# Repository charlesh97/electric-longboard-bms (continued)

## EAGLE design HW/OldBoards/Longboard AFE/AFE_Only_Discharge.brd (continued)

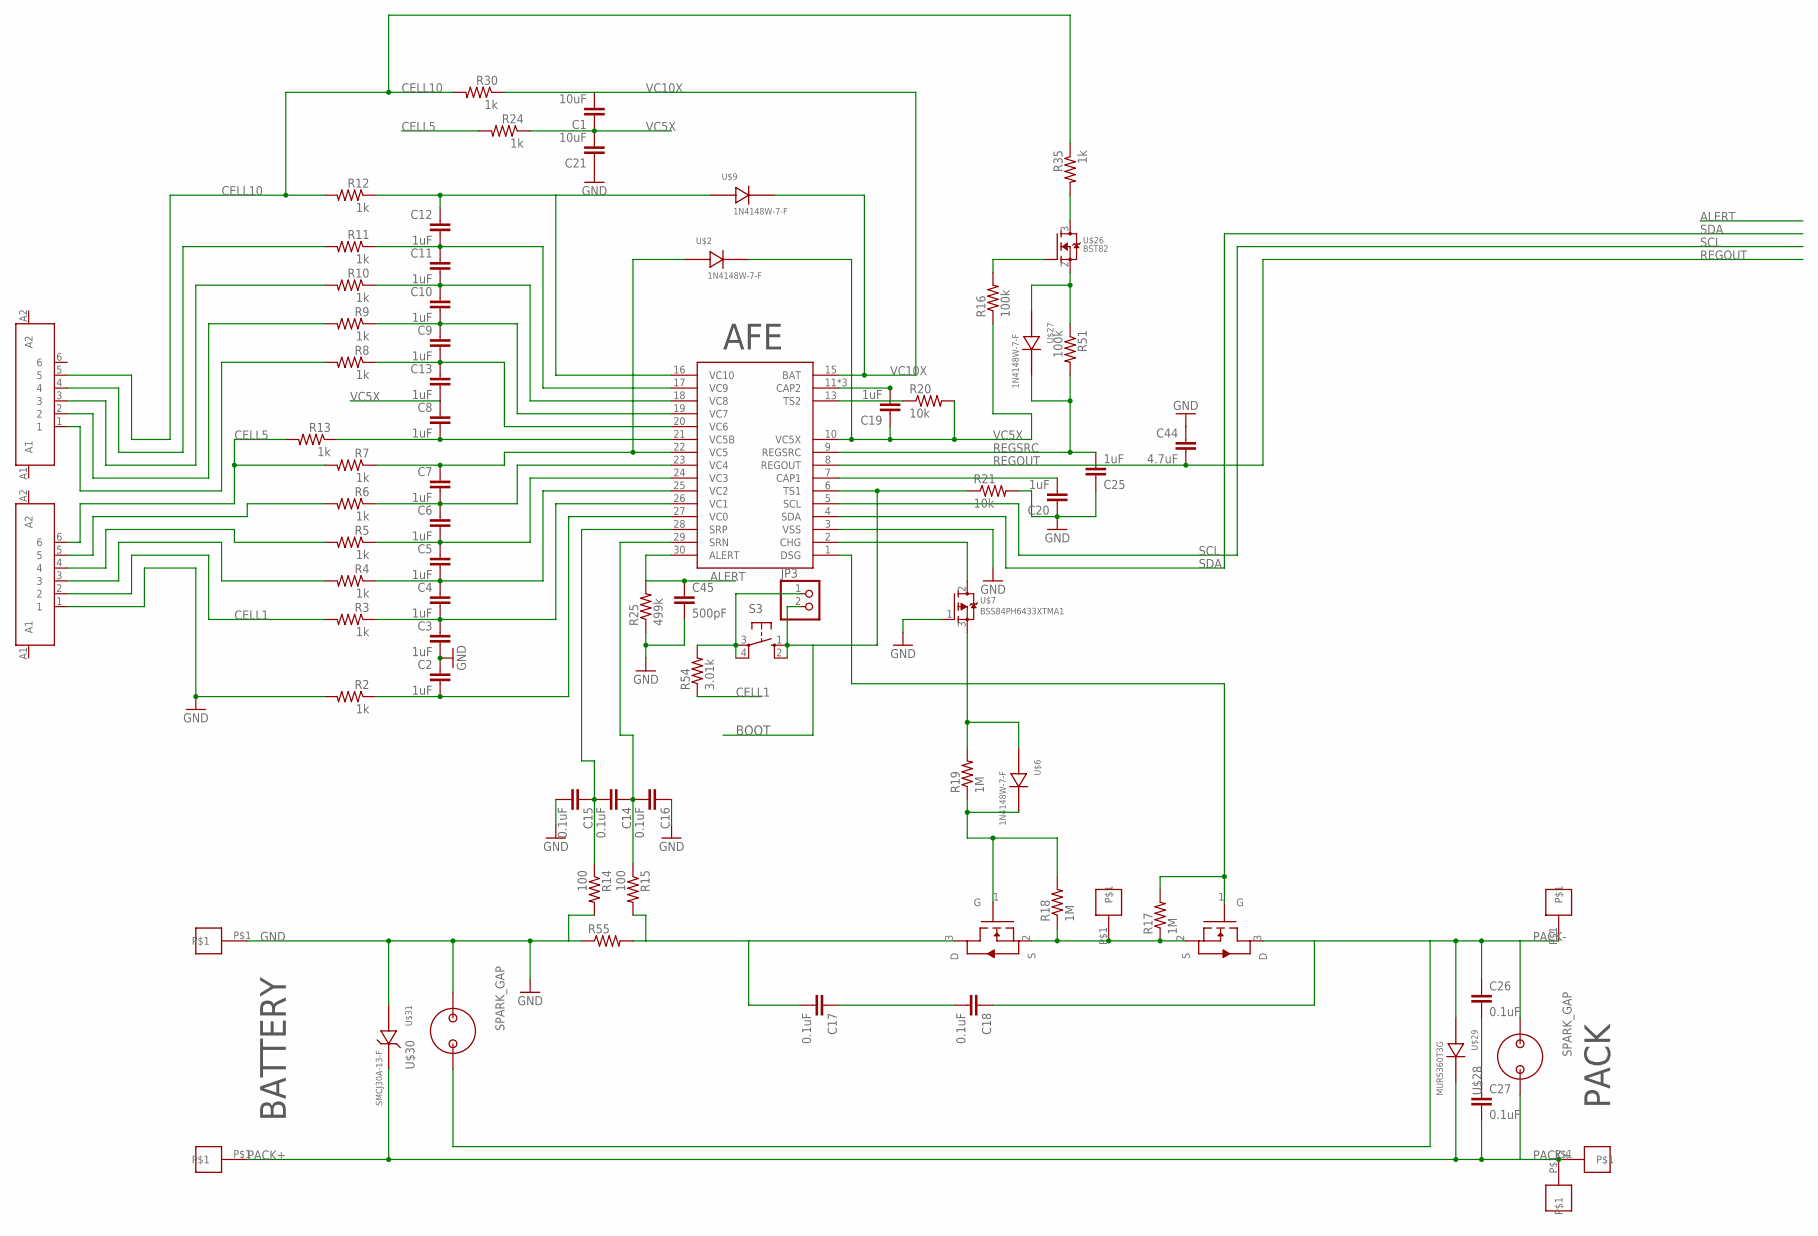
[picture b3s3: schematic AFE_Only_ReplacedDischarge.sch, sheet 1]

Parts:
C1, C21: 10uF; C1210
C2, C3, C4, C5, C6, C7, C8, C9, C10, C11, C12, C13, C19, C20, C25: 1uF; C0805
C14, C15, C16, C17, C18, C26, C27: 0.1uF; C0805
C44: 4.7uF; C0805
C45: 500pF; C0603
JP3: PINHD-1X2; 1X02
R2, R3, R4, R5, R6, R7, R8, R9, R10, R11, R12, R13, R24, R30, R35: 1k; R1206
R14, R15: 100; R0805
R16, R51: 100k; R0805
R17, R18, R19: 1M; R1206
R20, R21: 10k; R0805
R25: 499k; R0603
R54: 3.01k; R1206
R55: R-US_R2512; R2512
S3: 10-XX; B3F-10XX
U$1: BQ76930; SOIC-30
U$2, U$6, U$9, U$27: 1N4148W-7-F; SOD-123
U$3, U$35, U$36, U$37, U$38, U$39: PAD
U$4, U$5: AOB290L; TO-263
U$7: BSS84PH6433XTMA1; SOT23-3
U$24, U$33: JST_6PIN
U$26: BST82; SOT23-3
U$28, U$30: SPARK_GAP
U$29: MURS360T3G; SMC(DO-214AB)
U$31: SMCJ30A-13-F; SMB(DO-214AA)

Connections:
ALERT: C45.1, R25.2, U$1.30 (ALERT); also elsewhere on the board
BOOT: JP3.2, R21.1, S3.1 (S), S3.2 (S1), U$1.6 (TS1)
CELL1: R3.2, R54.1, U$33.2
CELL5: R7.2, R13.2, R24.2, U$33.6
CELL10: R12.2, R30.2, R35.1, U$24.5
GND: C2.1, C3.2, C15.2, C16.1, C20.1, C21.1, C25.1, C44.1, C45.2, R2.2, R14.2, R21.2, R25.1, R55.1, U$1.3 (VSS), U$3.P$1, U$7.1 (G), U$30.P$2, U$31.P$1 (1), U$33.1; also elsewhere on the board
unnamed: C3.1, C4.2, R3.1, U$1.26 (VC1)
unnamed: C4.1, C5.2, R4.1, U$1.25 (VC2)
unnamed: C5.1, C6.2, R5.1, U$1.24 (VC3)
unnamed: C6.1, C7.2, R6.1, U$1.23 (VC4)
unnamed: C7.1, R7.1, U$1.22 (VC5), U$2.P$1
unnamed: C8.2, R13.1, U$1.21 (VC5B)
unnamed: C9.1, C10.2, R9.1, U$1.19 (VC7)
unnamed: C10.1, C11.2, R10.1, U$1.18 (VC8)
unnamed: C11.1, C12.2, R11.1, U$1.17 (VC9)
unnamed: C12.1, R12.1, U$1.16 (VC10), U$9.P$1
unnamed: R5.2, U$33.4
unnamed: C2.2, R2.1, U$1.27 (VC0)
unnamed: C26.2, C27.1
unnamed: R4.2, U$33.3
unnamed: R6.2, U$33.5
unnamed: R8.2, U$24.1
unnamed: R9.2, U$24.2
unnamed: R10.2, U$24.3
unnamed: R11.2, U$24.4
unnamed: C9.2, C13.1, R8.1, U$1.20 (VC6)
unnamed: R16.2, U$26.1 (G)
unnamed: C20.2, U$1.7 (CAP1)
unnamed: C14.1, C16.2, R15.1, U$1.29 (SRN)
unnamed: JP3.1, R54.2, S3.3, S3.4 (P1)
unnamed: C14.2, C15.1, R14.1, U$1.28 (SRP)
unnamed: R18.2, R19.1, U$5.1 (G), U$6.P$2
unnamed: R19.2, U$6.P$1, U$7.3 (D)
unnamed: U$1.2 (CHG), U$7.2 (S)
unnamed: C17.1, C18.2
unnamed: C19.2, U$1.11 (CAP2), U$1.12 (CAP2), U$1.14 (CAP2)
unnamed: R20.1, U$1.13 (TS2)
unnamed: R51.1, U$26.2 (S), U$27.P$1
unnamed: R35.2, U$26.3 (D)
PACK+: C27.2, U$28.P$1, U$29.2, U$31.P$2 (2), U$35.P$1, U$36.P$1, U$39.P$1
REGOUT: C44.2, U$1.8 (REGOUT); also elsewhere on the board
REGSRC: C25.2, R51.2, U$1.9 (REGSRC), U$27.P$2
SCL: U$1.5 (SCL); also elsewhere on the board
SDA: U$1.4 (SDA); also elsewhere on the board
VC5X: C1.1, C8.1, C13.2, C19.1, C21.2, R16.1, R20.2, R24.1, U$1.10 (VC5X), U$2.P$2
VC10X: C1.2, R30.1, U$1.15 (BAT), U$9.P$2

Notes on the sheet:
BATTERY
PACK
AFE

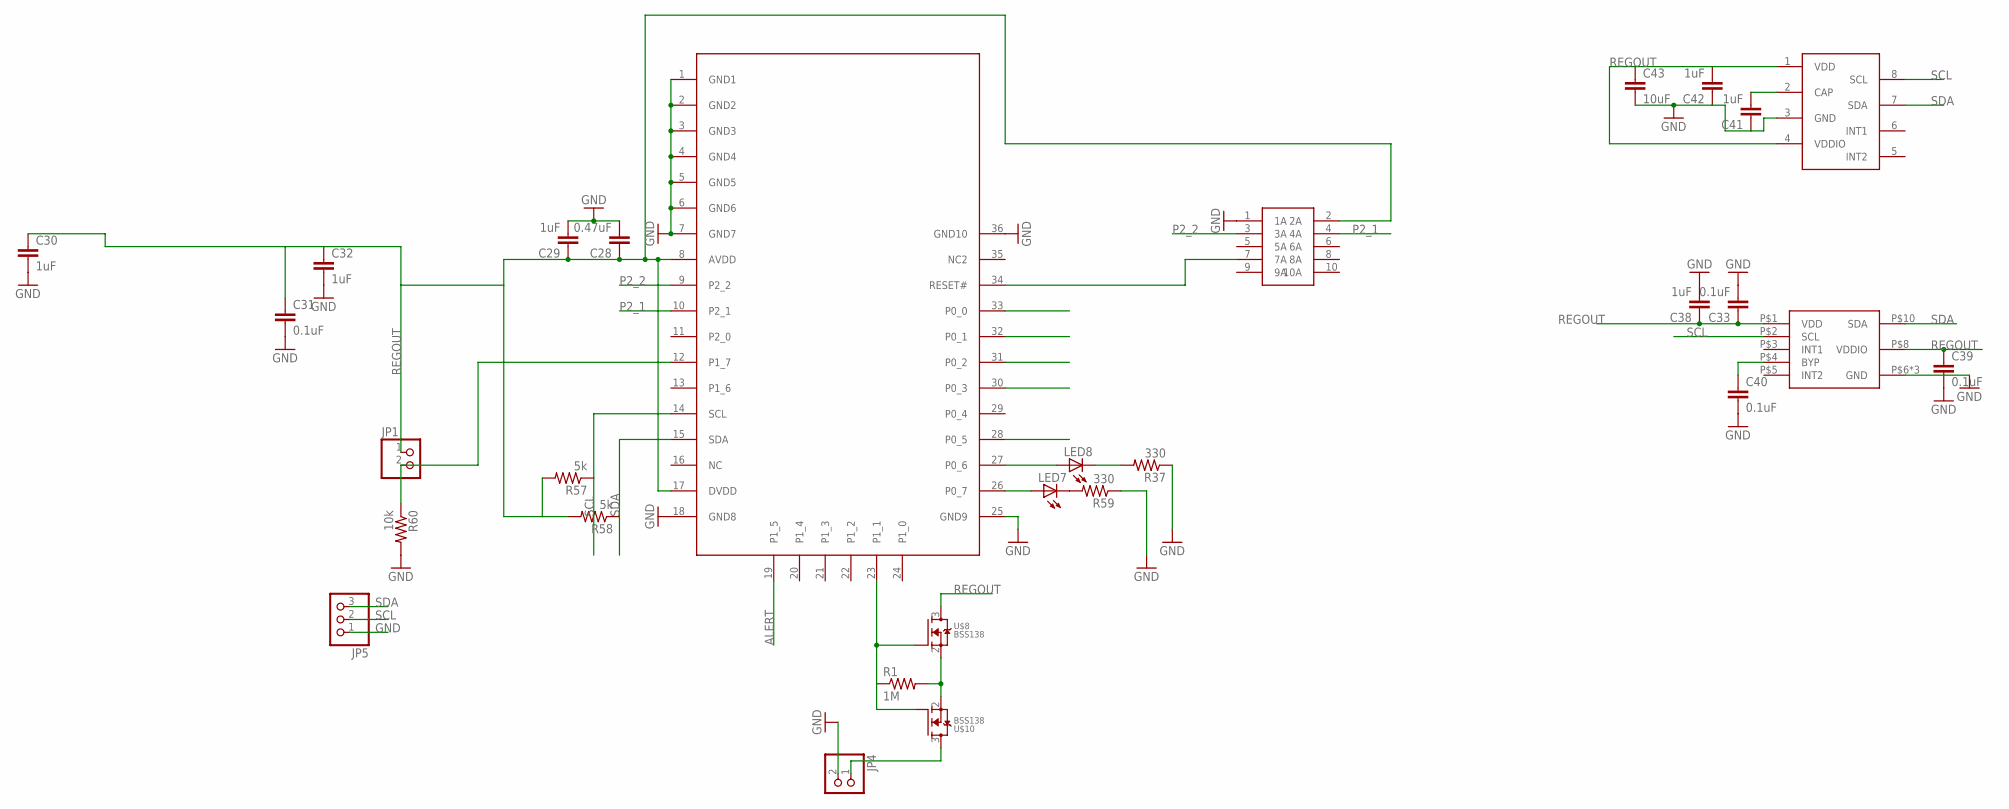
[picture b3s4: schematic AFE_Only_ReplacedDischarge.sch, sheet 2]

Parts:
C28: 0.47uF; C0402
C29, C30, C32, C38, C41, C42: 1uF; C0402
C31, C33, C39, C40: 0.1uF; C0402
C43: 10uF; C0603
JP1, JP4: PINHD-1X2; 1X02
JP5: PINHD-1X3; 1X03
LED7, LED8: LEDCHIP-LED0603; CHIP-LED0603
R1: 1M; R0402
R37, R59: 330; R0402
R57, R58: 5k; R0402
R60: 10k; R0402
U$8, U$10: BSS138; SOT23-3
U$20: BLE113; BLUEGIGA
U$22: RIBBON_10POS_MALE
U$25: MLP3115A2
U$32: MMA8653FC; 10-DFN2X2

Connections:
ALERT: U$20.19 (P1_5); also elsewhere on the board
CARD2: U$20.32 (P0_1)
CD: U$20.33 (P0_0)
CLK: U$20.28 (P0_5)
GND: C28.2, C29.2, C30.2, C31.2, C32.2, C33.2, C38.2, C39.2, C40.2, C41.1, C42.1, C43.2, JP4.2, JP5.1, R37.1, R59.1, R60.2, U$20.1 (GND1), U$20.2 (GND2), U$20.3 (GND3), U$20.4 (GND4), U$20.5 (GND5), U$20.6 (GND6), U$20.7 (GND7), U$20.18 (GND8), U$20.25 (GND9), U$20.36 (GND10), U$22.1 (1A), U$25.3 (GND), U$32.P$6 (GND), U$32.P$7 (GND), U$32.P$9 (GND); also elsewhere on the board
MISO: U$20.31 (P0_2)
MOSI: U$20.30 (P0_3)
unnamed: LED8.A, U$20.27 (P0_6)
unnamed: LED8.C, R37.2
unnamed: LED7.A, U$20.26 (P0_7)
unnamed: JP1.2, R60.1, U$20.12 (P1_7)
unnamed: LED7.C, R59.2
unnamed: U$20.34 (RESET#), U$22.7 (7A)
unnamed: C41.2, U$25.2 (CAP)
unnamed: C40.1, U$32.P$4 (BYP)
P2_1: U$20.10 (P2_1), U$22.4 (4A)
P2_2: U$20.9 (P2_2), U$22.3 (3A)
REGOUT: C28.1, C29.1, C30.1, C31.1, C32.1, C33.1, C38.1, C39.1, C42.2, C43.1, JP1.1, R57.2, R58.2, U$8.3 (D), U$20.8 (AVDD), U$20.17 (DVDD), U$22.2 (2A), U$25.1 (VDD), U$25.4 (VDDIO), U$32.P$1 (VDD), U$32.P$8 (VDDIO); also elsewhere on the board
SCL: JP5.2, R57.1, U$20.14 (SCL), U$25.8 (SCL), U$32.P$2 (SCL); also elsewhere on the board
SDA: JP5.3, R58.1, U$20.15 (SDA), U$25.7 (SDA), U$32.P$10 (SDA); also elsewhere on the board

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
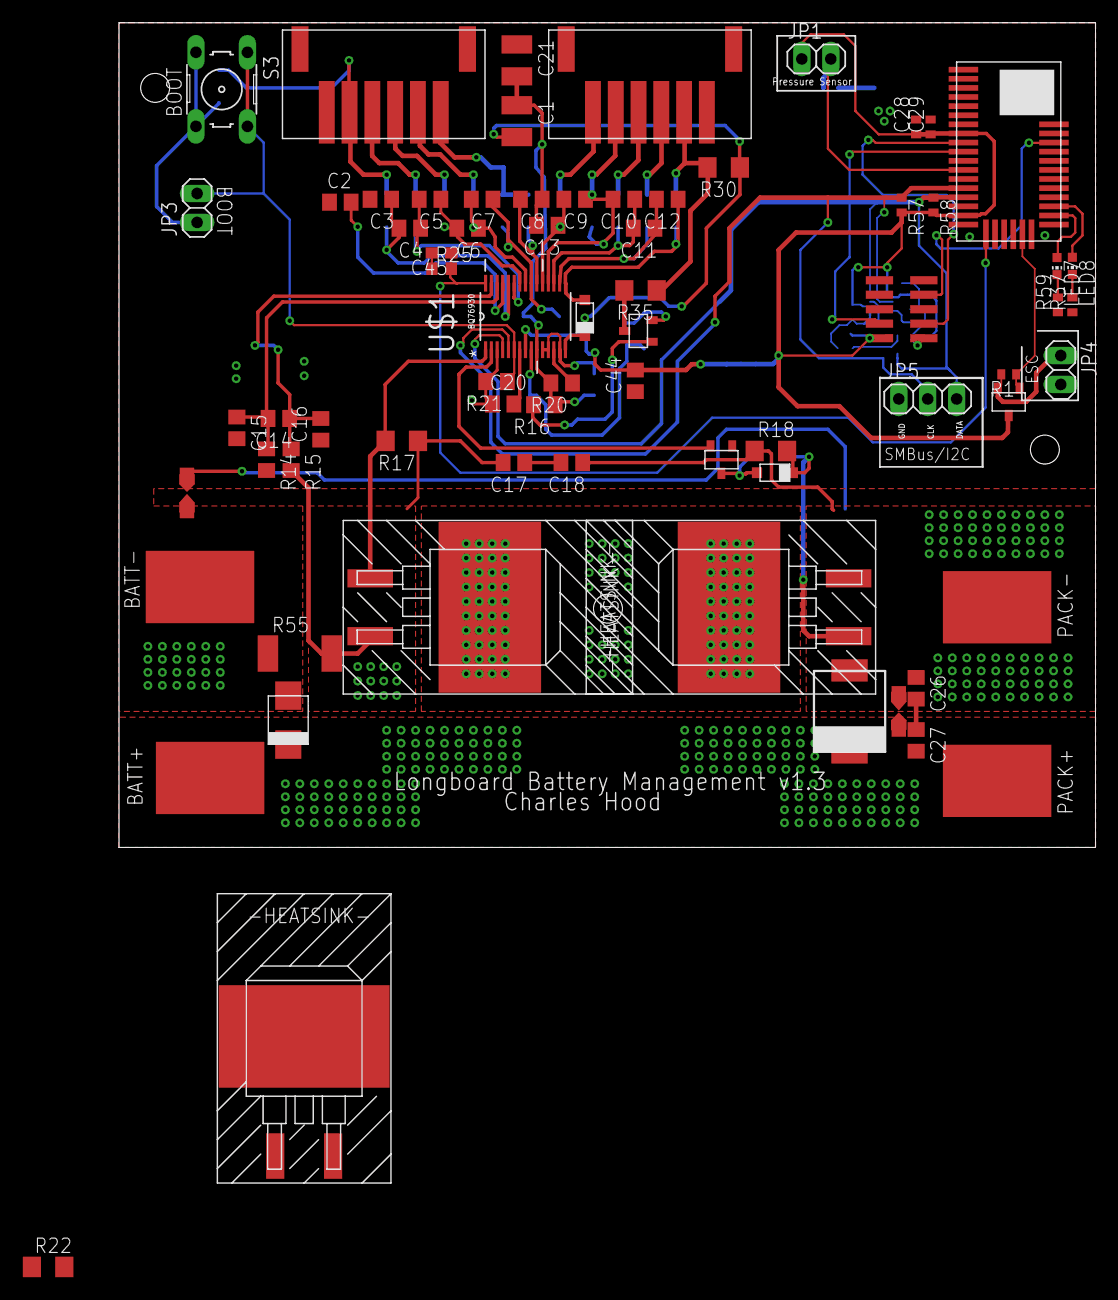
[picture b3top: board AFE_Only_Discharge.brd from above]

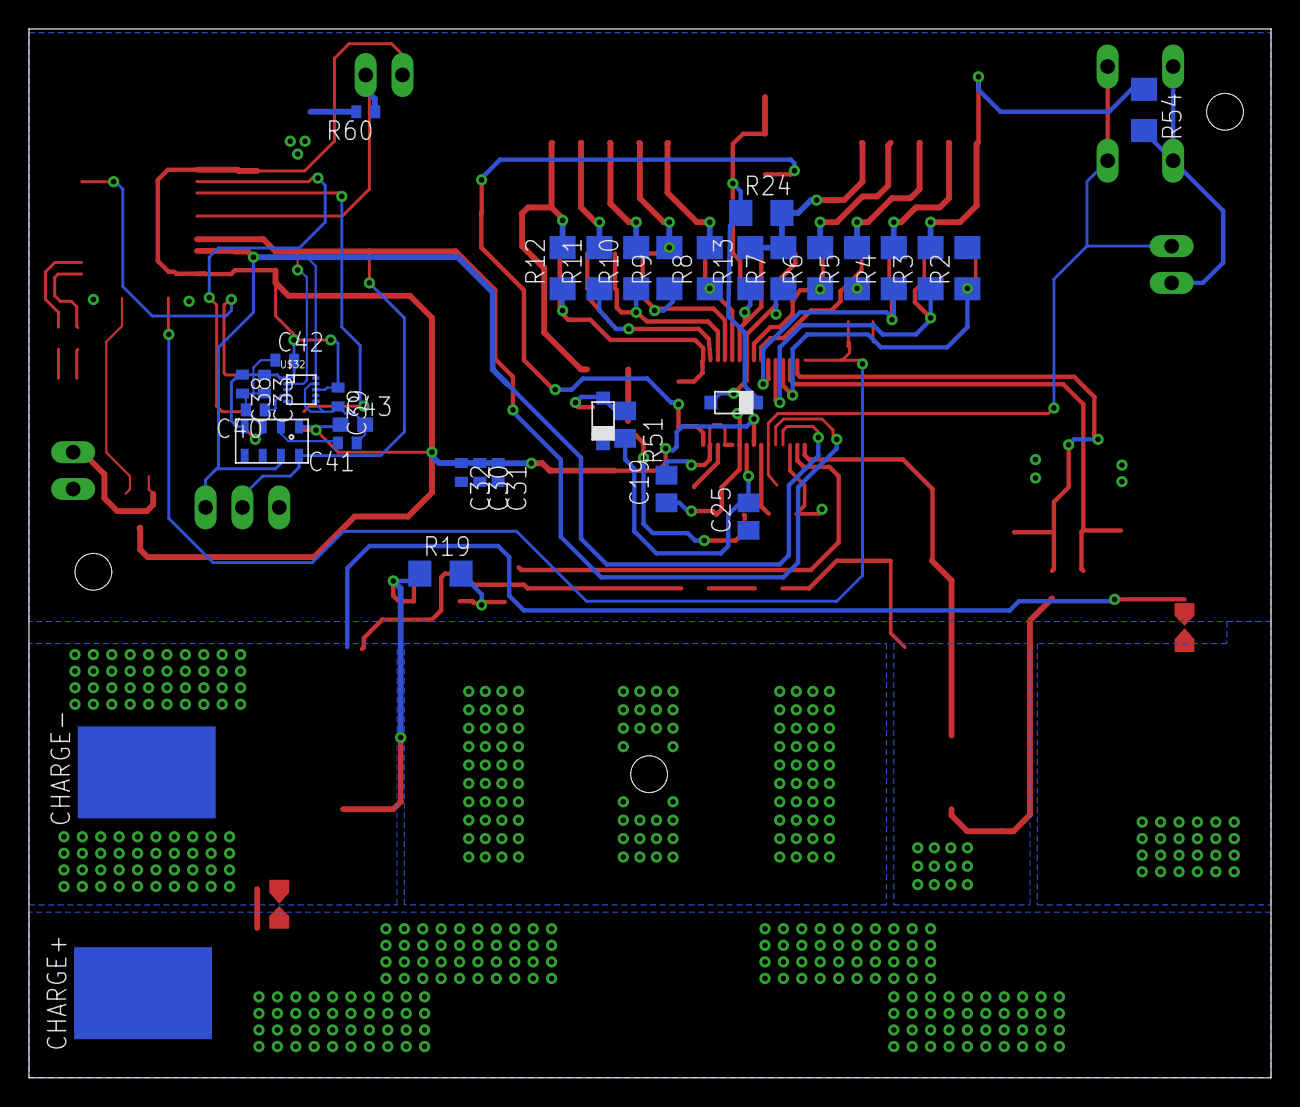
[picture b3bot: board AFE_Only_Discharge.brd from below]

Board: 2 copper layers, 85.7 x 72.4 mm, 106 parts (35 on the bottom side), 63 nets.

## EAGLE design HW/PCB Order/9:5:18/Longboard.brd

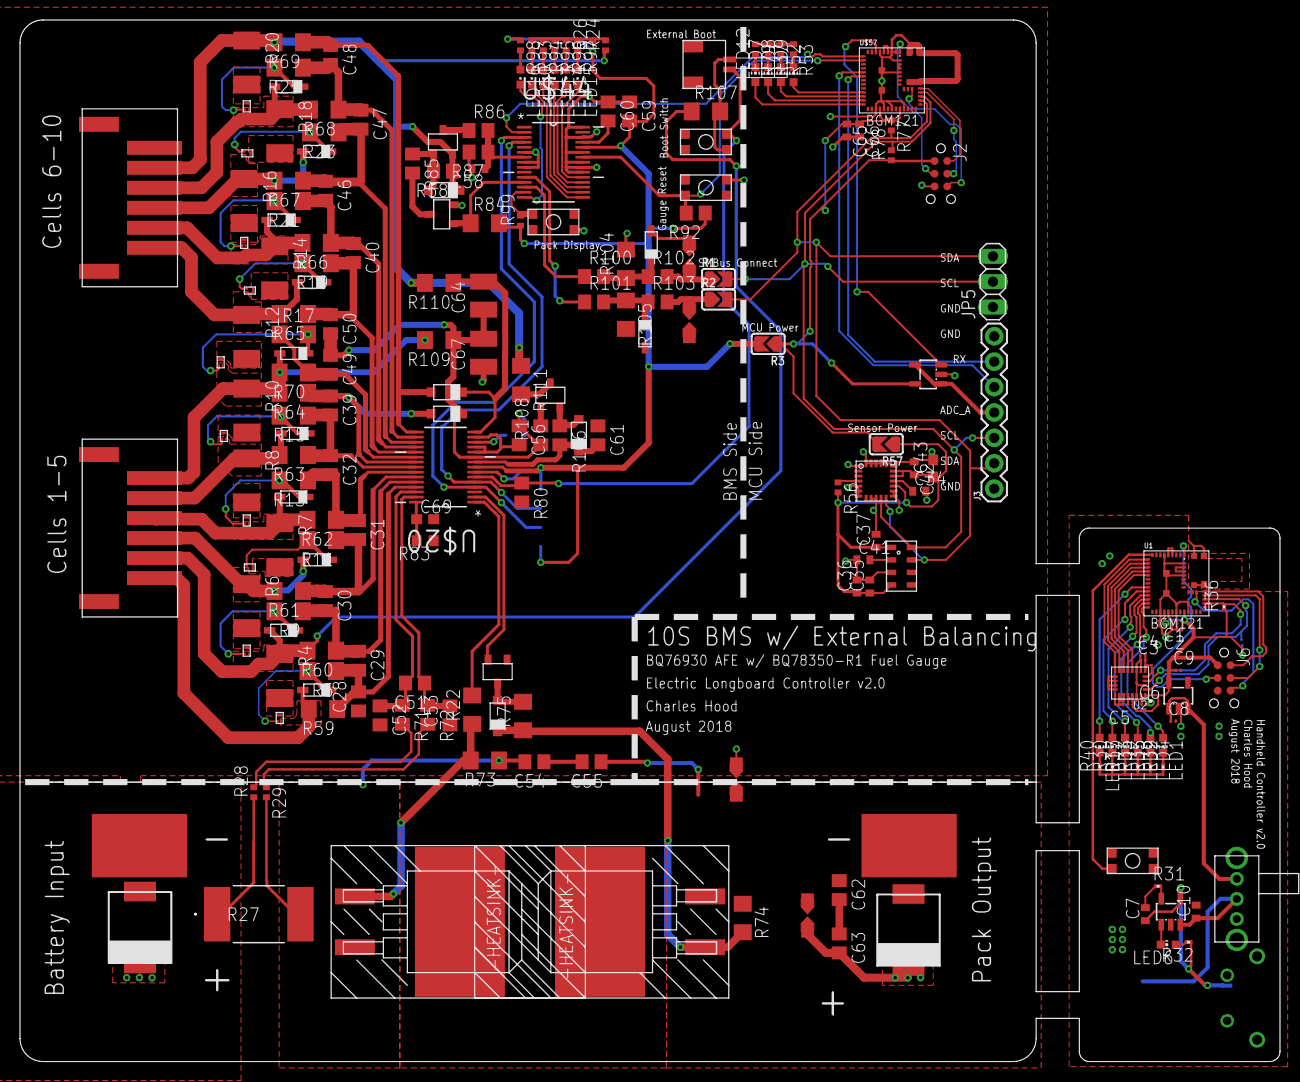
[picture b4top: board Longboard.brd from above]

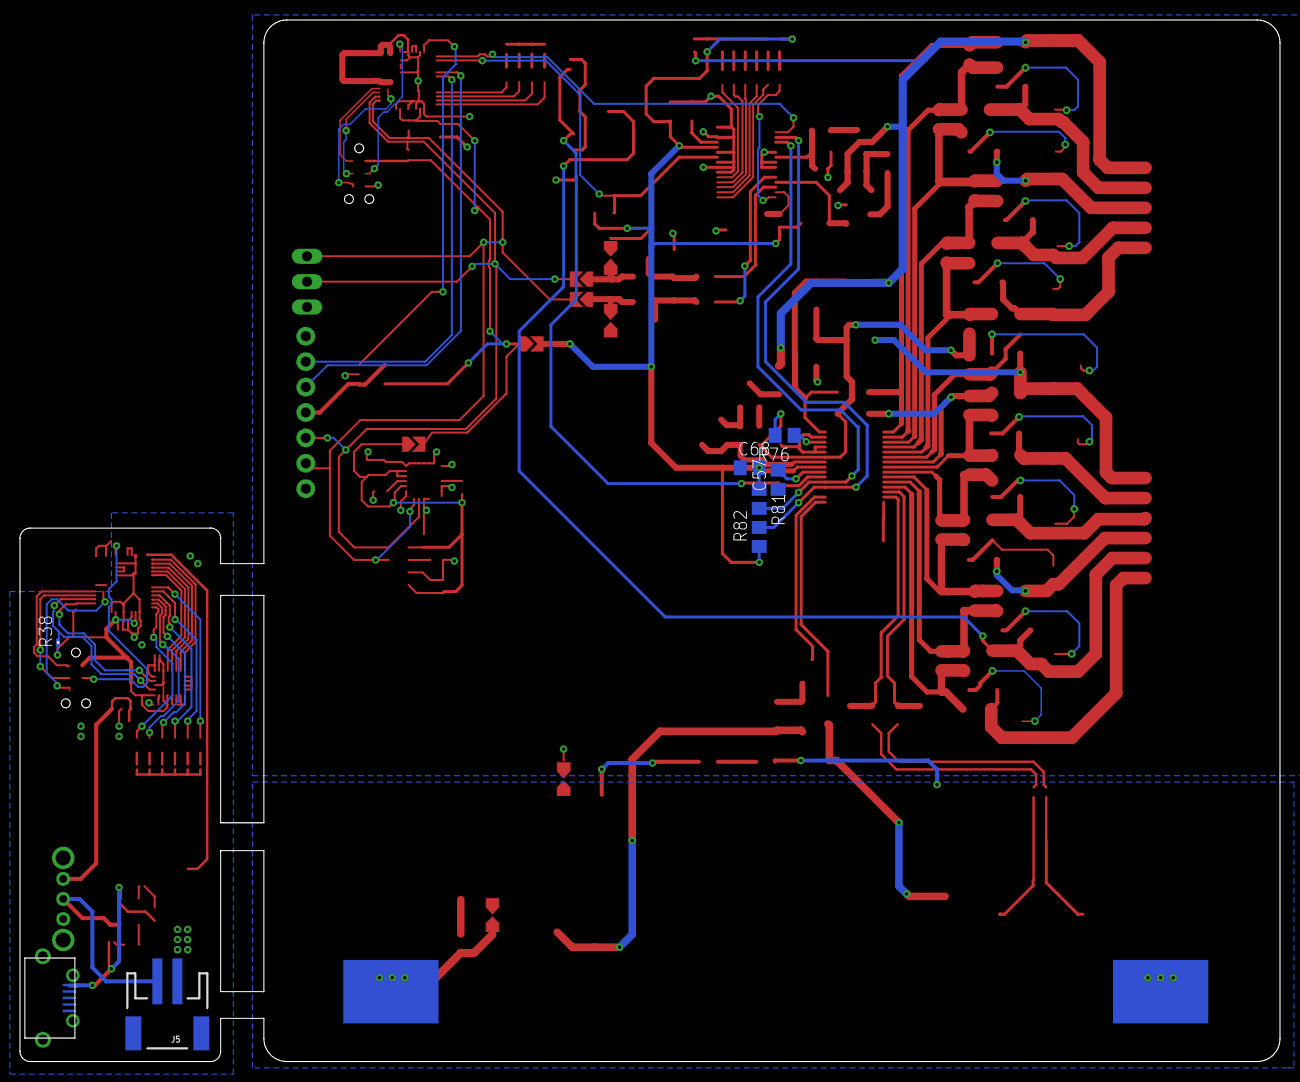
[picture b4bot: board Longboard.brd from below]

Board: 2 copper layers, 126.0 x 104.1 mm, 226 parts (10 on the bottom side), 163 nets.

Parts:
C1, C3, C4, C6: 0.1uF; C0201
C2, C8, C9: 1uF; C0201
C5: 0.01uF; C0201
C7, C10: 4.7uF; C0402
C28, C29, C30, C31, C32, C39, C40, C46, C47, C48, C49, C50: 0.22uF; C0805
C34, C37, C66: 0.1uF; C0402
C35, C41, C42, C65: 1uF; C0402
C36: 100nF; C0402
C43: 10uF; C0603
C51, C52, C53, C54, C55, C59, C60, C62, C63: 0.1uF; C0805
C56, C57, C61: 1uF; C0805
C58: 3300pF; C0402
C64, C67: 10uF; C1210
C68: 4.7uF; C0805
C69: 500pF; C0603
J1: JST_2PIN_SH
J2, J6: TC2030-MCP-NL
J3: 1X07
J4: MICRO_USB; MOLEX_USB
J5: JST-2-SMD
JP5: 1X03
LED1, LED2, LED3, LED4, LED5, LED6, LED7, LED8, LED9, LED12, LED17: CHIP-LED0603
LED10, LED11, LED13, LED14, LED15, LED16: CHIPLED_0603
Q1, Q3, Q4, Q5, Q6, Q7, Q8, Q9, Q10, Q11: CSD13381F4; 3-XFDFN
R1, R2, R3, R57: dnp; SOLDERJUMPER_ARROW_NOPASTE
R4, R6, R7, R8, R10, R12, R14, R16, R18, R20: 28.7; R2010
R5, R9, R11, R13, R15, R17, R19, R21, R23, R25: 10k; R1206
R22: 0; R1206
R24, R26: dnp; R0402
R27: WSLP39211L000FEB; W-3921
R28, R29: 0; R0402
R30, R33, R34, R35, R39, R40: 330; R0201
R31, R32, R36, R38: 4.7k; R0201
R37, R52, R53, R79, R93, R94, R95, R96, R97, R98: 330; R0402
R56: 47k; R0402
R58, R85, R92, R106, R108: 100k; R0805
R59, R60, R61, R62, R63, R64, R65, R66, R67, R68, R69, R70, R109, R110: 1k; R1206
R71, R72, R100, R101, R102, R103: 100; R0805
R73, R74, R75, R84, R104, R105: 1M; R1206
R76, R80, R81, R82: 10k; R0805
R77, R78: 4.7k; R0402
R83: 499k; R0603
R86: 300k; R0805
R87: 13.7k; R0805
R99: 100k; R0402
R107: 3.01k; R1206
R111: 200; R1206
S1, S2, S3, S4: KMR731NG
U1: BGM121_DEV; BGM121_PAC
U2: LSM9DS1; LGA24-8X4
U3: TPS782XX; SOT23-5L
U4: MCP73831; SOT23-5L
U$1: SPDT_THRU
U$3, U$4, U$6, U$7, U$8, U$9, U$10, U$11, U$12, U$13, U$50, U$51: MMSZ5232BS-7-F; SOD-323F
U$5: MCP6001; SOT23-5L
U$14, U$15, U$16, U$17: PAD
U$18, U$19: JST_6PIN
U$20: BQ76930; SOIC-30
U$21, U$40, U$43, U$55: 1N4148W-7-F; SOD-123
U$22, U$23: AOB290L; TO-263
U$25: MLP3115A2
U$34: FXAS21002
U$41: BSS84PH6433XTMA1; SOT23-3
U$44: BQ78350-R1; SOIC-30
U$45: NTR5105PT1G; SOT23-3
U$46: BSS138; SOT23-3
U$47: MMSZ5246B-7-F; SOD-123
U$52, U$53, U$56, U$59: SPARK_GAP
U$54: BST82; SOT23-3
U$57: BGM121_DEV; BGM121_PAC
U$58: MURS360T3G; SMC(DO-214AB)
U$60: SMCJ75A; SMC(DO-214AB)

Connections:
+3V1: C1.1, C2.1, C3.1, C4.1, C9.1, J6.1, R36.1, R38.1, U1.P$26, U1.P$31, U2.1, U2.3, U2.7, U2.8, U2.22, U2.23, U3.5
+3V3: C65.1, C66.1, J2.1, R3.1, R57.2, R77.1, R78.1, U$5.5, U$57.P$26, U$57.P$31
+3V3_SENSOR: C35.1, C36.1, C37.1, C42.2, C43.1, R56.2, R57.1, U$25.1, U$25.4, U$34.15, U$34.17, U$34.18
ACCEL/GYRO_EN: U1.P$10, U2.13
ALERT: C69.1, R83.2, U$20.30
BATT_IN: C10.1, J5.2, U4.3, U$1.2
BOOT: J1.2, R80.1, S1.P$2, U$20.6
CELL0: Q1.P$3, R59.2, U$6.1, U$19.1
CELL1: Q3.P$3, R4.1, R60.2, R107.1, U$3.1, U$19.2
CELL2: Q4.P$3, R6.1, R61.2, U$4.1, U$19.3
CELL3: Q5.P$3, R7.1, R62.2, U$7.1, U$19.4
CELL4: Q6.P$3, R8.1, R63.2, U$8.1, U$19.5
CELL5: Q7.P$3, R10.1, R64.2, R70.2, R109.2, U$9.1, U$19.6
CELL6: Q8.P$3, R12.1, R65.2, U$10.1, U$18.1
CELL7: Q9.P$3, R14.1, R66.2, U$11.1, U$18.2
CELL8: Q10.P$3, R16.1, R67.2, U$12.1, U$18.3
CELL9: Q11.P$3, R18.1, R68.2, U$13.1, U$18.4
CELL10: R20.1, R24.1, R58.1, R69.2, R110.2, R111.1, U$18.5, U$45.2, U$47.P$2
DBG_RESET: J2.3, U$57.P$1
DBG_RESET1: J6.3, U1.P$1
DBG_TCK_SWCLK: J2.4, U$57.P$39
DBG_TCK_SWCLK1: J6.4, U1.P$39
DBG_TDI_SWDIO: J2.2, U$57.P$40
DBG_TDI_SWDIO1: J6.2, U1.P$40
DBG_TDI_SWO: J2.6, U$57.P$41
DBG_TDI_SWO1: J6.6, U1.P$41
GAUGE_IRQ: U$44.2, U$57.P$10
GAUGE_RESET: R92.2, S3.P$4, U$44.24, U$57.P$11
GAUGE_SCL: R81.2, U$20.5, U$44.4
GAUGE_SDA: R82.2, U$20.4, U$44.3
GND: C28.1, C34.2, C35.2, C36.2, C37.2, C41.1, C42.1, C43.2, C52.2, C53.1, C57.1, C58.2, C59.1, C60.1, C61.1, C65.2, C66.2, C67.1, C68.1, C69.2, J2.5, J3.1, J3.7, JP5.1, R27.1, R28.1, R37.1, R52.1, R53.1, R79.1, R80.2, R83.1, R87.2, R104.2, R105.2, S2.P$3, S3.P$2, U$5.2, U$17.P$1, U$18.6, U$18.A1, U$18.A2, U$19.A1, U$19.A2, U$20.3, U$25.3, U$34.1, U$34.5, U$34.6, U$34.7, U$34.9, U$34.10, U$34.13, U$34.14, U$34.19, U$34.20, U$34.21, U$34.22, U$34.23, U$34.24, U$41.1, U$44.6, U$44.8, U$44.9, U$44.21, U$44.22, U$44.23, U$44.25, U$44.28, U$44.30, U$46.2, U$50.1, U$51.1, U$52.P$1, U$53.P$1, U$57.P$2, U$57.P$3, U$57.P$6, U$57.P$25, U$57.P$27, U$57.P$29, U$57.P$32, U$57.P$47, U$57.P$50, U$57.P$51, U$57.P$52, U$57.P$53, U$57.P$54, U$57.P$55, U$57.P$56, U$59.P$2, U$60.1
GND1: C1.2, C2.2, C3.2, C4.2, C5.2, C6.2, C7.2, C8.2, C9.2, C10.2, J4.P$5, J5.1, J6.5, R30.1, R31.1, R33.1, R34.1, R35.1, R39.1, R40.1, S4.P$4, U1.P$2, U1.P$3, U1.P$6, U1.P$25, U1.P$27, U1.P$29, U1.P$32, U1.P$47, U1.P$50, U1.P$51, U1.P$52, U1.P$53, U1.P$54, U1.P$55, U1.P$56, U2.5, U2.6, U2.14, U2.15, U2.16, U2.17, U2.18, U2.19, U2.20, U3.2, U3.4, U4.2
IRQ1: U1.P$12, U2.11
IRQ2: U1.P$11, U2.12
IRQ3: U1.P$14, U2.9
IRQ4: U1.P$13, U2.10
MCU_DAC_OUT: U$5.3, U$57.P$7
unnamed: LED12.A, U$57.P$22
unnamed: LED7.A, U$57.P$21
unnamed: LED8.A, U$57.P$20
unnamed: LED9.A, U$57.P$19
unnamed: R28.2, R71.2
unnamed: R29.1, R72.2
unnamed: Q1.P$1, R4.2
unnamed: Q8.P$2, R19.2, U$10.2
unnamed: Q1.P$2, R5.2, U$6.2
unnamed: Q3.P$1, R6.2
unnamed: Q3.P$2, R9.2, U$3.2
unnamed: R22.2, U$20.1
unnamed: Q5.P$1, R8.2
unnamed: Q4.P$1, R7.2
unnamed: Q4.P$2, R11.2, U$4.2
unnamed: Q5.P$2, R13.2, U$7.2
unnamed: Q6.P$2, R15.2, U$8.2
unnamed: Q8.P$1, R14.2
unnamed: C40.2, C50.1, R19.1, R65.1, U$20.20
unnamed: C49.2, R17.1, R70.1, U$20.21
unnamed: R24.2, R26.2, R93.1, R94.1, R95.1, R96.1, R97.1
unnamed: Q6.P$1, R10.2
unnamed: LED1.C, R39.2
unnamed: LED4.C, R33.2
unnamed: Q7.P$1, R12.2
unnamed: Q7.P$2, R17.2, U$9.2
unnamed: Q9.P$1, R16.2
unnamed: LED2.C, R34.2
unnamed: R56.1, U$34.4
unnamed: LED5.C, R35.2
unnamed: Q10.P$1, R18.2
unnamed: Q11.P$1, R20.2
unnamed: Q11.P$2, R25.2, U$13.2
unnamed: Q10.P$2, R23.2, U$12.2
unnamed: LED7.C, R37.2
unnamed: Q9.P$2, R21.2, U$11.2
unnamed: LED1.A, U1.P$22
unnamed: LED4.A, U1.P$21
unnamed: LED2.A, U1.P$20
unnamed: LED5.A, U1.P$19
unnamed: LED8.C, R52.2
unnamed: LED3.C, R30.2
unnamed: LED3.A, U1.P$18
unnamed: C5.1, U2.21
unnamed: C6.1, U2.24
unnamed: C7.1, J4.P$1, R32.1, U4.4
unnamed: R31.2, U4.5
unnamed: LED6.A, R32.2
unnamed: LED6.C, U4.1
unnamed: U1.P$4, U1.P$5
unnamed: U1.P$48, U1.P$49
unnamed: S4.P$2, U1.P$9
unnamed: LED17.C, R40.2
unnamed: LED17.A, U1.P$17
unnamed: LED9.C, R53.2
unnamed: C29.1, C30.2, R9.1, R60.1, U$20.26
unnamed: C30.1, C31.2, R11.1, R61.1, U$20.25
unnamed: C31.1, C32.2, R13.1, R62.1, U$20.24
unnamed: C34.1, U$34.16
unnamed: C32.1, C39.2, R15.1, R63.1, U$20.23
unnamed: C39.1, R64.1, U$20.22, U$21.P$1
unnamed: C41.2, U$25.2
unnamed: C40.1, C46.2, R21.1, R66.1, U$20.19
unnamed: C46.1, C47.2, R23.1, R67.1, U$20.18
unnamed: C47.1, C48.2, R25.1, R68.1, U$20.17
unnamed: C48.1, R69.1, U$20.16, U$43.P$1
unnamed: C28.2, C29.2, R5.1, R59.1, U$20.27
unnamed: C51.1, C53.2, R72.1, U$20.29
unnamed: C51.2, C52.1, R71.1, U$20.28
unnamed: C54.2, R27.2, R29.2, R73.1, U$22.2
unnamed: U$22.3, U$23.3
unnamed: R74.2, R75.1, U$23.1, U$40.P$2
unnamed: R75.2, U$40.P$1, U$41.3
unnamed: U$20.2, U$41.2
unnamed: C54.1, C55.2
unnamed: C56.2, U$20.11, U$20.12, U$20.14
unnamed: R76.1, U$20.13
unnamed: C57.2, U$20.7
unnamed: R84.1, U$44.12, U$46.1
unnamed: R85.2, U$46.3
unnamed: U$57.P$4, U$57.P$5
unnamed: LED12.C, R79.2
unnamed: U$57.P$48, U$57.P$49
unnamed: R58.2, R85.1, U$45.1, U$47.P$1
unnamed: R86.1, U$45.3
unnamed: C58.1, R86.2, R87.1, U$44.7
unnamed: C60.2, U$44.27
unnamed: LED10.A, R93.2
unnamed: LED11.A, R94.2
unnamed: LED13.A, R95.2
unnamed: LED14.A, R96.2
unnamed: LED15.A, R97.2
unnamed: LED10.C, U$44.16
unnamed: LED11.C, U$44.17
unnamed: LED13.C, U$44.18
unnamed: LED14.C, U$44.19
unnamed: LED15.C, U$44.20
unnamed: LED16.A, R98.2
unnamed: R99.2, S2.P$1, U$44.14
unnamed: LED16.C, U$44.15
unnamed: R101.1, U$44.11
unnamed: R100.1, U$44.13
unnamed: R100.2, R102.1, R104.1, U$50.2
unnamed: R101.2, R103.1, R105.1, U$51.2
unnamed: R106.1, U$54.2, U$55.P$1
unnamed: R111.2, U$54.3
unnamed: R22.1, R73.2, U$22.1
unnamed: J1.1, R107.2, S1.P$3
unnamed: C62.2, C63.1
unnamed: R108.2, U$54.1
PACK+: C63.2, U$15.P$1, U$16.P$1, U$56.P$1, U$58.2, U$60.2
PACK-: C55.1, C62.1, R74.1, U$14.P$1, U$23.2, U$56.P$2, U$58.1, U$59.P$1
POWER_IN: C8.1, U3.1, U3.3, U$1.3
REGOUT: C59.2, C68.2, R3.2, R26.1, R81.1, R82.1, R84.2, R92.1, R98.1, R99.1, U$20.8, U$44.26
REGSRC: C61.2, R106.2, U$20.9, U$55.P$2
SCL: J3.3, JP5.2, R1.2, R78.2, U$25.8, U$34.11, U$57.P$38
SCL1: R38.2, U1.P$38, U2.2
SDA: J3.2, JP5.3, R2.2, R77.2, U$25.7, U$34.12, U$57.P$37
SDA1: R36.2, U1.P$37, U2.4
SMBC: R1.1, R102.2, U$53.P$2
SMBD: R2.1, R103.2, U$52.P$2
UART_RX: J3.6, U$57.P$15
UART_TX: J3.5, U$57.P$14
VC5X: C49.1, C50.2, C56.1, C64.1, C67.2, R76.2, R108.1, R109.1, U$20.10, U$21.P$2
VC10X: C64.2, R110.1, U$20.15, U$43.P$2
VESC_ADC_CONTROL_A: J3.4, U$5.1, U$5.4
